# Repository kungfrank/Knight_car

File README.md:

# Knight_car

## Introduction

This repository contains all the software that runs on the Knightcar.

Knightcar is a low-cost platform base on raspberry pi 3, comes with rpi3 official camera, wide-angle len, and YDlidar for learning autonomous robot.

## reference

MIT duckietown : https://github.com/duckietown/Software

NCTU duckietown : https://github.com/Duckietown-NCTU/Software

## Demo Video

Navigation Demo Video: https://www.youtube.com/watch?v=UlBHKnV47X4

## Developer

*PouChun, Kung (k3083518729@gmail.com)

## Usage & Tutorial

Medium Notes: https://medium.com/@k3083518729/k-bot-a218c075e2ee

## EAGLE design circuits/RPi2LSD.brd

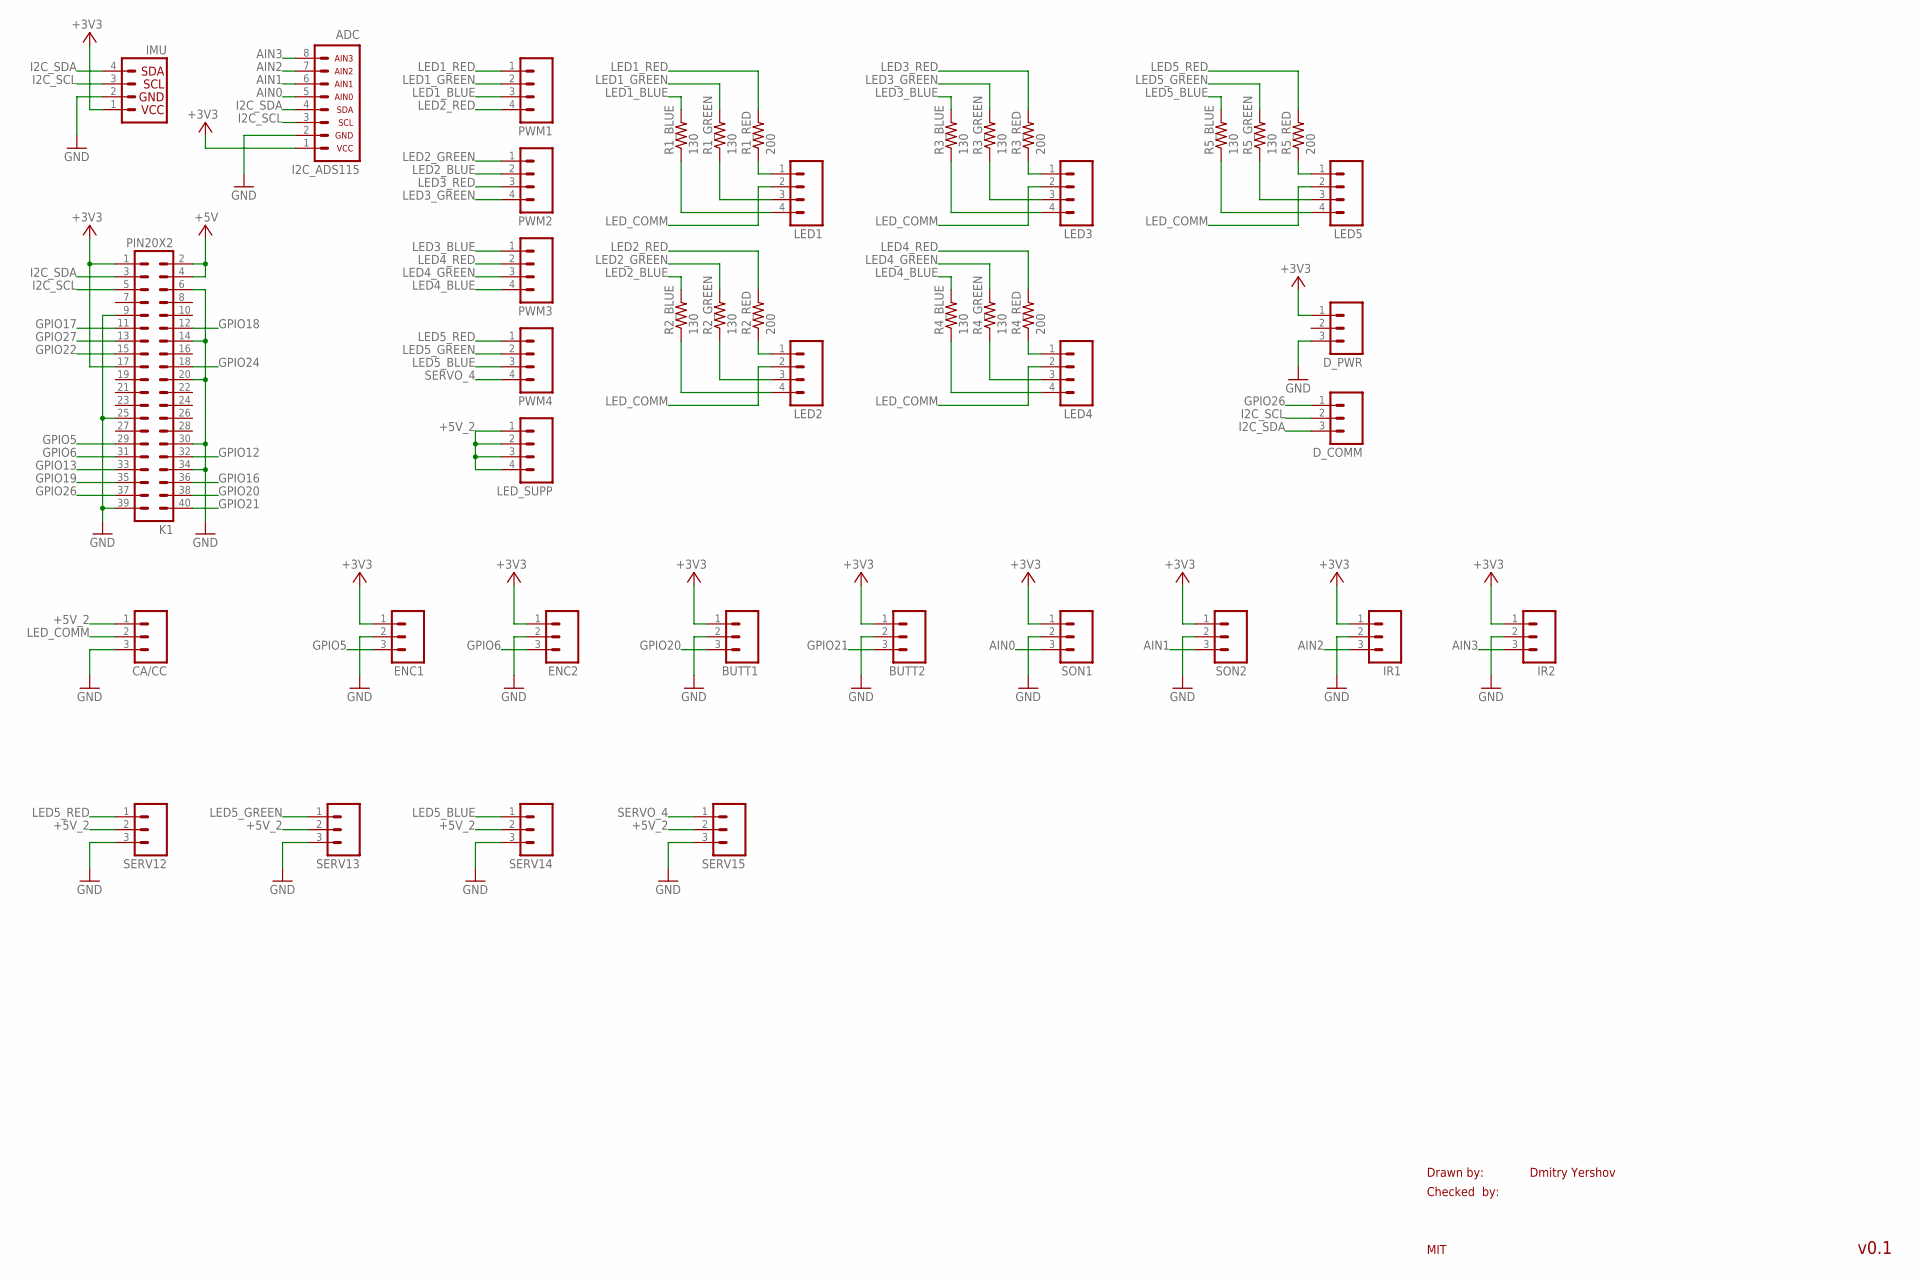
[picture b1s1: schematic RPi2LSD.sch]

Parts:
ADC: I2C_ADS115; I2C_AX4
BUTT1, BUTT2: M03PTH; 1X03
CA/CC: M03PTH; 1X03
D_COMM: M03PTH; 1X03
D_PWR: M03PTH; 1X03
ENC1, ENC2: M03PTH; 1X03
IMU: I2C_IMU_L3GD20H+LSM303; 1X04
IR1, IR2: M03PTH; 1X03
K1: PIN20X2; PIN_20X2
LED1, LED2, LED3, LED4, LED5: M04PTH; 1X04
LED_SUPP: M041X04_NO_SILK; 1X04_NO_SILK
PWM1, PWM2, PWM3, PWM4: M041X04_NO_SILK; 1X04_NO_SILK
R1_BLUE, R1_GREEN, R2_BLUE, R2_GREEN, R3_BLUE, R3_GREEN, R4_BLUE, R4_GREEN, R5_BLUE, R5_GREEN: 130; 0207/9
R1_RED, R2_RED, R3_RED, R4_RED, R5_RED: 200; 0207/9
SERV12, SERV13, SERV14, SERV15: M03PTH; 1X03
SON1, SON2: M03PTH; 1X03

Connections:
+3V3: ADC.1, BUTT1.1, BUTT2.1, D_PWR.1, ENC1.1, ENC2.1, IMU.1, IR1.1, IR2.1, K1.1, K1.17, SON1.1, SON2.1
+5V: K1.2, K1.4
+5V_2: CA/CC.1, LED_SUPP.1, LED_SUPP.2, LED_SUPP.3, LED_SUPP.4, SERV12.2, SERV13.2, SERV14.2, SERV15.2
AIN0: ADC.5, SON1.3
AIN1: ADC.6, SON2.3
AIN2: ADC.7, IR1.3
AIN3: ADC.8, IR2.3
GND: ADC.2, BUTT1.2, BUTT2.2, CA/CC.3, D_PWR.3, ENC1.2, ENC2.2, IMU.2, IR1.2, IR2.2, K1.6, K1.9, K1.14, K1.20, K1.25, K1.30, K1.34, K1.39, SERV12.3, SERV13.3, SERV14.3, SERV15.3, SON1.2, SON2.2
GPIO5: ENC1.3, K1.29
GPIO6: ENC2.3, K1.31
GPIO12: K1.32
GPIO13: K1.33
GPIO16: K1.36
GPIO17: K1.11
GPIO18: K1.12
GPIO19: K1.35
GPIO20: BUTT1.3, K1.38
GPIO21: BUTT2.3, K1.40
GPIO22: K1.15
GPIO24: K1.18
GPIO26: D_COMM.1, K1.37
GPIO27: K1.13
I2C_SCL: ADC.3, D_COMM.2, IMU.3, K1.5
I2C_SDA: ADC.4, D_COMM.3, IMU.4, K1.3
LED1_BLUE: PWM1.3, R1_BLUE.2
LED1_GREEN: PWM1.2, R1_GREEN.2
LED1_RED: PWM1.1, R1_RED.2
LED2_BLUE: PWM2.2, R2_BLUE.2
LED2_GREEN: PWM2.1, R2_GREEN.2
LED2_RED: PWM1.4, R2_RED.2
LED3_BLUE: PWM3.1, R3_BLUE.2
LED3_GREEN: PWM2.4, R3_GREEN.2
LED3_RED: PWM2.3, R3_RED.2
LED4_BLUE: PWM3.4, R4_BLUE.2
LED4_GREEN: PWM3.3, R4_GREEN.2
LED4_RED: PWM3.2, R4_RED.2
LED5_BLUE: PWM4.3, R5_BLUE.2, SERV14.1
LED5_GREEN: PWM4.2, R5_GREEN.2, SERV13.1
LED5_RED: PWM4.1, R5_RED.2, SERV12.1
LED_COMM: CA/CC.2, LED1.2, LED2.2, LED3.2, LED4.2, LED5.2
unnamed: LED1.4, R1_BLUE.1
unnamed: LED1.3, R1_GREEN.1
unnamed: LED1.1, R1_RED.1
unnamed: LED2.4, R2_BLUE.1
unnamed: LED2.3, R2_GREEN.1
unnamed: LED2.1, R2_RED.1
unnamed: LED3.4, R3_BLUE.1
unnamed: LED3.3, R3_GREEN.1
unnamed: LED3.1, R3_RED.1
unnamed: LED4.4, R4_BLUE.1
unnamed: LED4.3, R4_GREEN.1
unnamed: LED4.1, R4_RED.1
unnamed: LED5.4, R5_BLUE.1
unnamed: LED5.3, R5_GREEN.1
unnamed: LED5.1, R5_RED.1
SERVO_4: PWM4.4, SERV15.1

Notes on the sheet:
Drawn by:
Checked by:
MIT
Dmitry Yershov
v0.1

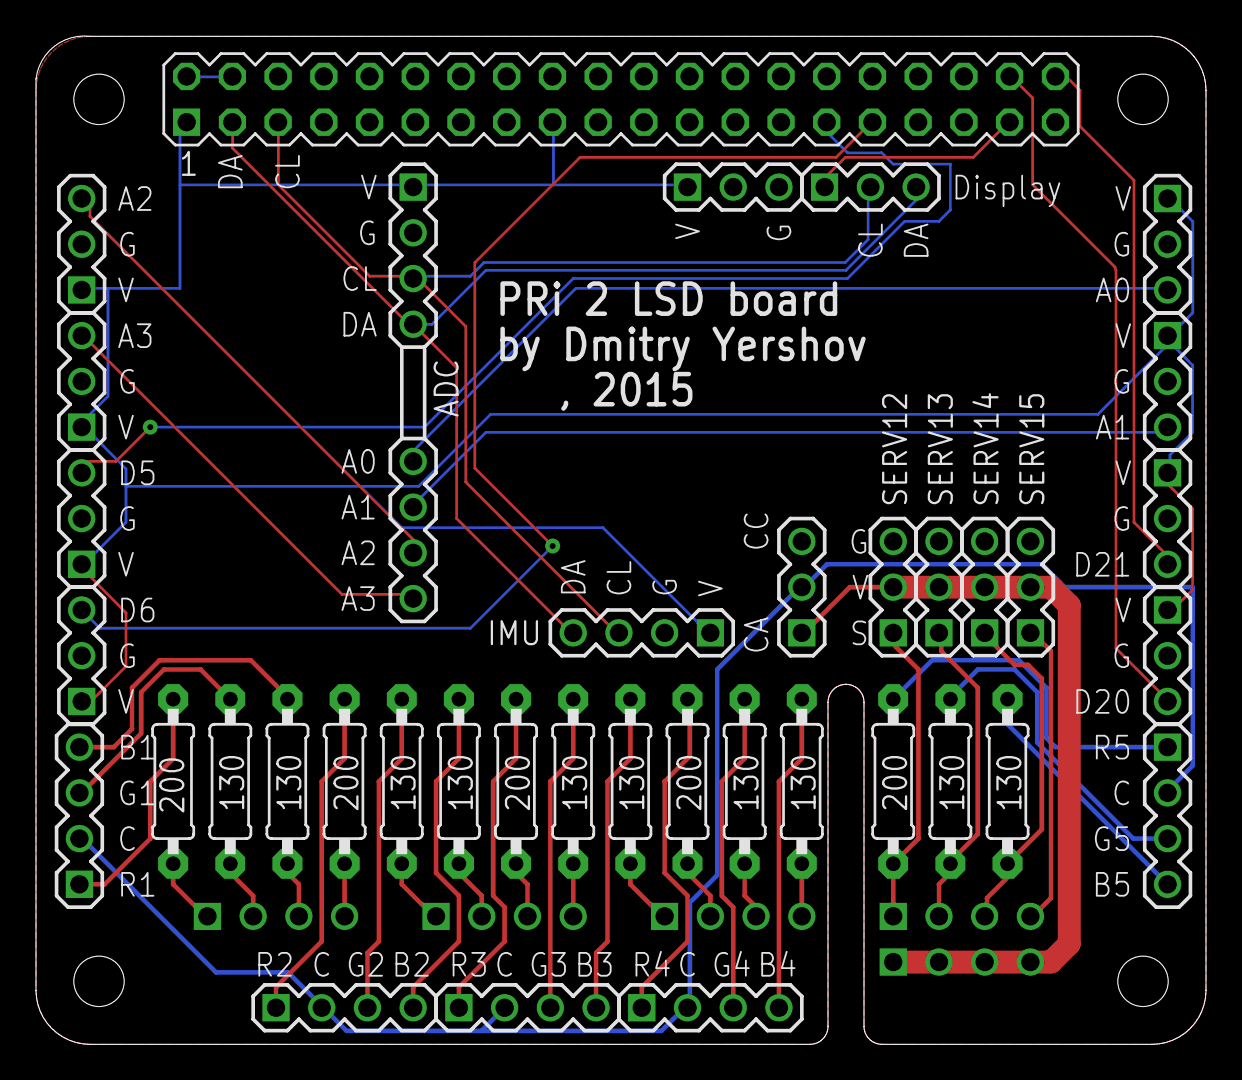
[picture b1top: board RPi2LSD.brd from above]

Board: 2 copper layers, 65.0 x 56.0 mm, 43 parts (0 on the bottom side), 47 nets.

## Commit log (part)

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2016-05-12 duckiebot camera calibration
2016-05-13 fix color correction allowed for bad transforms
    empirically tested to reject bad transformations for when lane markings are not visible. Removing FIXME!! comment
2016-05-14 add IEEE latex template
2016-05-19 add opencv-cpp-template; need to work on launch files
2016-05-21 add mocapXX units to scuderia.yaml
2016-05-21 rm unnecessary headers and src code
2016-05-21 read ~veh param
2016-05-22 add mac addresses for mocap01-04
2016-05-23 update trabant camera intrinsic yaml
2016-05-23 add extrinsic parameter for trabant
2016-05-23 add trabant wheel calibration yaml
2016-05-23 add mocap05-08 mac addresses to scuderia.yaml
2016-05-23 add include directory for trabant opencv_cpp_template
2016-05-24 decode compressed image message in callback
2016-05-25 calibration robotics
2016-05-26 add mocap camera param files
2016-05-26 mocap08 camera intrinsic
2016-05-26 mocap01 camera intrinsic
2016-05-26 mocap03 camera intrinsic
2016-05-26 mocap02 camera intrinsic
2016-05-26 mocap07 camera intrinsic
2016-05-26 mocap06 camera intrinsic
2016-05-26 mocap04 camera intrinsic
2016-05-31 red_detector(copy face_detector)
2016-05-31 duckietown_nctu.xacro
2016-06-01 osramex
2016-06-01 osram camera calibration
2016-06-03 change mocap.yaml to 1280x960; add mocap package including upstart and launch file
2016-06-03 use as default veh
2016-06-04 update pandola car config
2016-06-05 change mocap settings
2016-06-06 pandola tutorial G
2016-06-06 update mocap settings
2016-06-07 wheel calibration & red_detection(redBulls) update
2016-06-07 plate recognition
2016-06-10 calibration
2016-06-14 alphaduck-apriltag tracking
2016-06-14 undistort node in C++
2016-06-14 add example
2016-06-14 kinematic calibration add
2016-06-16 resolve duckietown_kfc package.xml problem
2016-06-26 fix a little bug of red detector
2016-06-26 kinematics alphaduck
2016-06-28 fix apriltags_ros
2016-07-01 add arg_nctu for assistive robotics group team
2016-07-01 phnix camera & wheel calib
2016-07-01 add jcarname to scuderia
2016-07-01 phnix ros package
2016-07-01 machine-fix
2016-07-04 rm machines
2016-07-05 add package
2016-07-05 add yaml files:add kaku to scuderia
2016-07-06 jack camera calibration
2016-07-06 duckietown camera calibration
2016-07-07 jack_duckiebot
2016-07-11 jack
2016-07-11 fix package
2016-07-13 add new files
2016-07-20 jerry's file update
2016-07-21 karissa update scuderia.yml
2016-07-21 update calibration
2016-07-24 change header files with <>
2016-07-24 comment out parts of grasseater imgundist that prevent compiling on RPi2
2016-07-24 comment out grasseater campicpp/imgpreproc that prevent compiling on RPi2
2016-08-11 calibration_gain
2016-08-11 Lane_following along with only YELLOW
2016-08-12 uncomment duckietown_msgs
2016-08-14 kenny camera calibration
2016-08-14 sean camera intrinsic calibration
2016-08-17 add intrinsic calibration file of lebeast
2016-08-17 add intrinsic calibration file of julie
2016-08-18 vehicle_follow_jack
2016-08-18 vehicle_follow_jack.launch
2016-08-18 some stupid change
2016-08-30 add caroline
2016-08-30 moving slam to attic
2016-08-30 adding isam to repo
2016-09-01 sean camera calibration
2016-09-17 face_following_sean v1
2016-09-22 ignore isam
2016-09-28 add fall2016 & tutorial folders
2016-10-11 init commit for python tutorial
2016-10-11 add tutorial.ipynb
2016-10-14 tutorials add opencv
2016-10-16 fot lane_following
2016-10-16 for lane_following
2016-10-17 modify tutorial.ipynb
2016-10-20 topbot camera calibration
2016-10-24 add lane filter ipynb
2016-10-24 agribot camera calibration
2016-10-24 one two threee stop
2016-10-28 buyme camera calibration
2016-10-29 add SCP to fall2016_nctu
2016-10-29 soukoban camera calibration
2016-10-30 hercules camera calibration
2016-10-31 add lane_filter2 ipynb and test image
2016-10-31 imu_test_sean
2016-10-31 scuderia
2016-10-31 Car14
2016-11-03 carryou camera calibration
2016-11-04 assignment1
2016-11-06 add extra credit info
2016-11-07 littlecar camera calibration
2016-11-14 duckiebot wheel calibration
2016-11-16 calibration for caroline
2016-11-19 Adafruit_IMU Sean
2016-11-19 adafruit_imu_sean_v1
2016-11-19 adafruit_imu_sean v1
2016-11-19 adafruit_imu_sean v2
2016-11-19 adafruit_imu_sean v3
2016-11-19 adafruit_imu_sean v4
2016-11-19 adafruit_imu_sean onShutdown
2016-11-19 adafruit_imu_sean v5
2016-11-22 csp_2016 hw1
2016-11-22 add csp 2016 hw1
2016-11-22 remove some wrong file
2016-11-23 yunbot camera calibration
2016-11-24 other rpy
2016-11-24 temperature/humdity sensor
2016-11-24 indent
2016-11-24 indent fixed
2016-11-24 done
2016-11-27 add testing images to notebook
2016-11-27 add code to tutorial with face, circlepattern, duckie, mser
2016-11-28 modify timeit to time
2016-11-28 face_detector_tutorial
2016-11-28 student's jpg
2016-11-29 add image
2016-11-29 HW1_images
2016-11-29 image name modify
2016-11-29 0310768
2016-11-29 rm .ipynb_checkpoint
2016-11-29 add .gitignore for tutorial/python
2016-11-29 add 02-drive without joystick
2016-11-30 blackmanba camera calibration
2016-12-01 add Voronoi and BFS, A*
2016-12-03 add motion example
2016-12-03 jupyter car_cmd subscriber
2016-12-04 add motion planing example
2016-12-08 add 03 tutorial fsm
2016-12-08 add yellow_only
2016-12-08 fsm test
2016-12-08 add lane filter states to subscribe fsm state
2016-12-09 add fsm file name param; joystick_jupyter.launch
2016-12-09 comment out joystick jupyter by conflict of inverse kinematic node
2016-12-09 add jupyter control state
2016-12-09 add jupyter state modification
2016-12-09 jupyter_control state
2016-12-11 add param for car_cmd_switch into AGV.launch and AGV_master.launch
2016-12-11 send car_cmd_switch message and at_stop_line event
2016-12-12 imu_sean
2016-12-14 add Right & Left lane_following in FSM
2016-12-17 add mocap boundary warning example
2016-12-18 car15 calibration add
2016-12-18 scuderia.yaml
2016-12-18 test
2016-12-18 add mocap motion planning
2016-12-18 mocap forward point example
2016-12-18 add spinning and forward x
2016-12-19 fsm Turn Right & Left with Timer
2016-12-20 lcm to ros pose
2016-12-20 remove lcm2ros
2016-12-23 mocap_jack
2016-12-24 for final project
2016-12-25 mocap_jupyter_control
2016-12-25 add duckiebot state publisher
2016-12-26 minor updates for wording
2016-12-29 add machine
2016-12-29 namespace modify
2016-12-29 add mocap.launch
2016-12-30 add state pose publisher
2016-12-30 modify state pose publisher
2016-12-31 modify state_pose_publisher of tango
2017-01-02 rm csp2016
2017-01-02 add street navi fsm
2017-01-02 add transition of left turn and right turn
2017-01-03 lanewidth_modification
2017-01-03 modify namespace
2017-01-04 add patrol
2017-01-04 add patrol function
2017-01-04 Patrol_mode_normal_NBJK
2017-01-04 little_waiter
2017-01-07 mocap_25spin test_v1
2017-01-12 add car:teng
2017-01-12 add TagRectDetector
2017-01-12 modification for China
2017-01-12 add teng's calibration
2017-01-13 Robot Raconteur Host for driving the duckiebot
2017-01-13 remove tabs and replace with spaces
2017-01-13 make executable
2017-01-13 fixed some additional typos and missing links to get the service to work
2017-01-13 Adding Robot Raconteur Service
2017-01-13 Updated RR service to add lane pose and AR tag detections
2017-01-13 updated to launch the april tags postprocessing node and extract the tag ID. currently untested
2017-01-13 updating duckie_client
2017-01-13 Couple of fixes / updates
2017-01-13 didn't mean to change duckie_client. reverting and adding gitignore so that doesn't happen again
2017-01-13 restructure of duckie_rr_bridge. It isn't a python module
2017-01-13 adding back the gitignore so students updating duckie_client don't keep getting prompted to commit it
2017-01-13 removing files since RR bridge is not a python module
2017-01-13 add Gripper Kit
2017-01-13 add badminton detector
2017-01-19 duckietown_sean
2017-01-21 mocap01 calibrattion revised
2017-01-21 modify mocap patrol suitable for cloud
2017-01-24 modify mocap patrol into two part
2017-01-24 modify timer to general version
2017-01-26 add fsm switch to text-navigation
2017-01-31 add itri-tactile at tutorial/python
2017-02-01 repair timer and left-right-turn lane_filer
2017-02-03 modify fsm to open quad proposals
2017-02-04 add ieee template in sean and kenny's folders
2017-02-04 add bibtex in sean's folder
2017-02-04 add ref in kenny's folder
2017-02-08 for gw line
2017-02-08 lane_following for gw line
2017-02-09 add url link to bibtex
2017-02-09 rm unwanted commits
2017-02-09 rm unwnated commits
2017-02-10 qwer camera calibration
2017-02-13 yellow_blue line
2017-02-13 using compress for apriltags
2017-02-13 add switch to apriltag
2017-02-14 yellow blue line
2017-02-14 blue_yellow_detector
2017-02-14 modify blue_yellow_detector
2017-02-14 add spring2017_nctu folder
2017-02-14 add trabant to spring2017_nctu
2017-02-15 create blue_yellow launch file
2017-02-15 modify lines_finder
2017-02-15 fixed error
2017-02-15 add car_cmd_publisher
2017-02-15 modify mocap patrol
2017-02-15 fix yellow_blue_detector
2017-02-16 add anti_histogram
2017-02-16 add config file for blue_yellow detector
2017-02-16 change file path
2017-02-20 add anaconda2.bash into tutorial/python
2017-02-22 add process time
2017-03-15 add color line detector
2017-03-15 modify yellow_blue_detector
2017-03-15 modify color_detector
2017-03-15 modify color_detector.launch
2017-03-16 fixed color detector
2017-03-22 fixed blue_yellow_following
2017-03-23 add color for footwear
2017-03-23 fix color number
2017-03-23 fixed no lines stop
2017-03-23 finish Pedestrian stop
2017-03-24 move stop function to timer
2017-03-24 fix timer for fw_lane_following
2017-03-26 add gitignore for bitbuckiet repo
2017-03-28 add no_lines detect
2017-03-29 change calibration for the nwe mount
2017-03-29 joystick_contol fsm
2017-03-29 add camera_mount controller
2017-03-29 add camera_mount rotation
2017-04-01 comment stop_line_filter in joystick control state
2017-04-05 add joystick state
2017-04-05 modify camera mount
2017-04-06 for guide dog launch
2017-04-06 add gc in the scuderia
2017-04-08 add python tutorial to send Twist to Gazebo vehicle
2017-04-17 add tutorial jupyter notebook ransac
2017-04-18 add spiderbot scuderia.
2017-04-19 add encoder_publisher
2017-04-19 add u-turn to fsm
2017-04-22 rename tutorial ransac -> ransac icp
2017-04-24 add icp example to python tutorial
2017-04-25 launch for guidedog
2017-04-26 launch for guidedog logdata
2017-04-26 for joystick
2017-04-26 joystick and camera launch
2017-04-30 add icp-answer
2017-05-02 add gcleft in scuderia
2017-05-02 add gcright in scuderia
2017-05-02 modify the scuderia
2017-05-02 remove the wrong file
2017-05-03 add encoder_publusher
2017-05-18 camera_mount update
2017-05-18 add ros_to_gazebo system
2017-05-18 rm backup file
2017-05-21 add guide-dog
2017-05-23 control real robot from gazebo
2017-05-25 fix bug about controlling motor
2017-05-25 fix bug
2017-07-03 preparation for summer school
2017-07-05 color line detector which can change the color of line you are going to follow.
2017-07-15 add summer school jupyter notebooks; modified from Eric's SumS17.git, assignment1, and car command tutorial
2017-07-16 correction for the image path in images path
2017-07-16 add group photos in 6-1 objdetector of jupyternotebook
2017-07-16 put some questions of false positives, cases.
2017-07-16 summer school update
2017-07-16 jupyter car command testing and comment guassian filter
2017-07-24 add rqt-dynamic param and remove scu
2017-07-24 modify dynamic_pid
2017-07-24 modify gazebo_car_cmd node and dynamic pid
2017-08-01 ignore guidedog-code
2017-08-01 add virtual_joystick to control virtual robot
2017-08-03 add MIT_ROBOT_lab2 in duckietown
2017-08-03 fix bug with mitlab2
2017-08-03 modify virtual2real
2017-08-05 wheel odometry node and launch files
2017-08-05 wheel odometry readme
2017-08-09 adafruit imu sean
2017-08-22 implement PURE PURSUIT in Gazebo
2017-09-08 sean_scp_ipynb
2017-09-08 add gazebo_gripper_mode & ros smach
2017-09-21 make a action server to run CPS
2017-12-21 update fsm graphviz path
2018-03-16 add pkg_name && modify env.sh
2018-03-16 add pkg_name&modified environment.sh
2018-03-16 add setup
2018-03-20 change create-machines.py
2018-05-24 SLAM&NAV commit
2018-05-30 update max_rot_vel (5/30)

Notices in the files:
parts and their libraries:
SparkFun-Connectors: Licensing: Creative Commons ShareAlike 4.0 International - https://creativecommons.org/licenses/by-sa/4.0
